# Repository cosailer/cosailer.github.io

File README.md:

cosailer.github.io
==================

welcome to my small site about my projects :-)

you can view this site at http://cosailer.github.io/

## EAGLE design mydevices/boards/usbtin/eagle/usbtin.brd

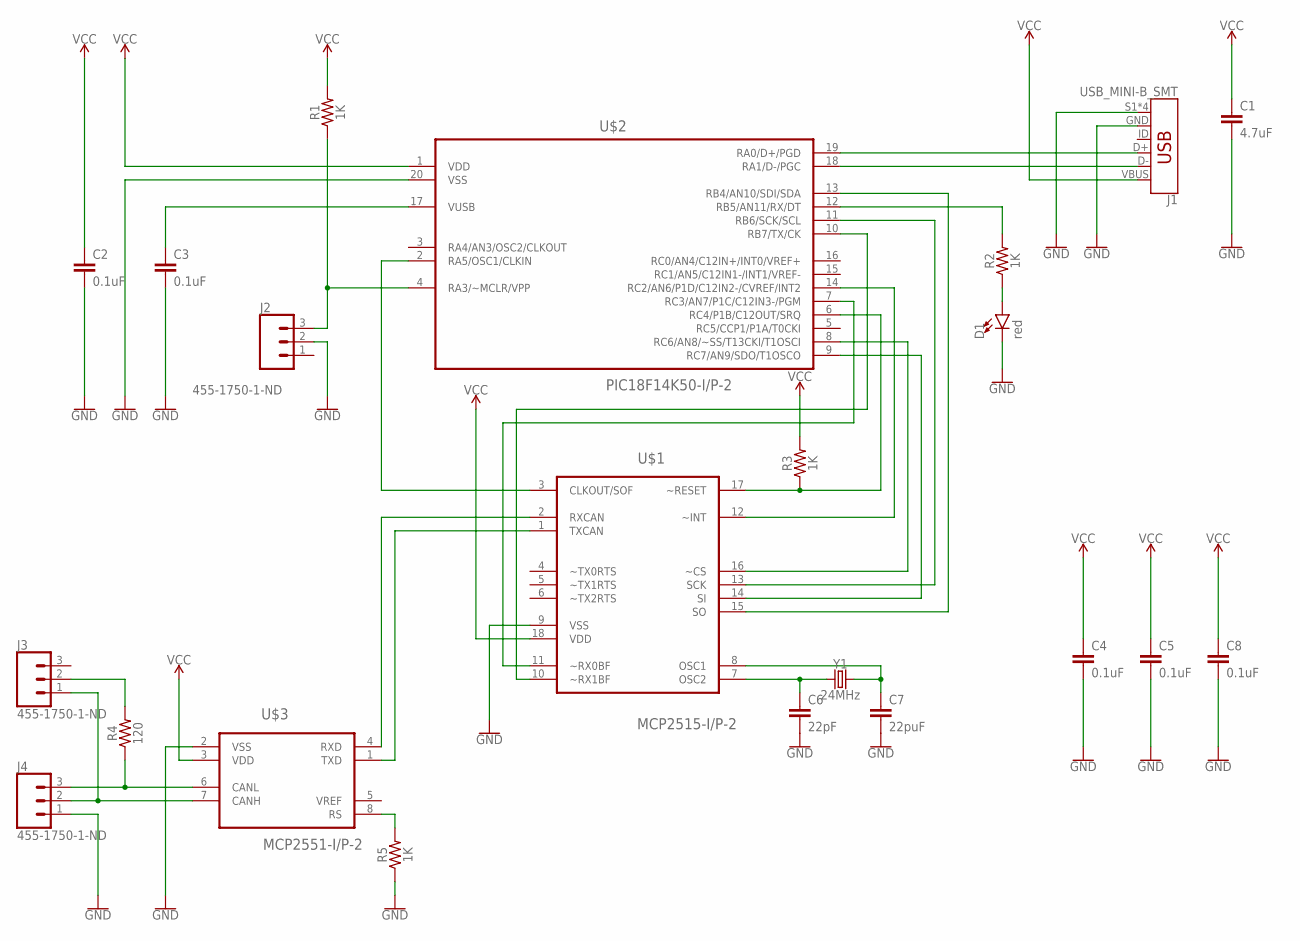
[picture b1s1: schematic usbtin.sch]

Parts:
C1: 4.7uF; 1206
C2, C3, C4, C5, C8: 0.1uF; 0603
C6: 22pF; 0805
C7: 22puF; 0805
D1: red; LED-1206
J1: USB_MINI-B_SMT; USB-MINIB
J2, J3, J4: 455-1750-1-ND; 1X03
R1, R2, R3, R5: 1K; 0805
R4: 120; 0805
U$1: MCP2515-I/P-2; DIP254P762X432-18
U$2: PIC18F14K50-I/P-2; DIP254P762X533-20
U$3: MCP2551-I/P-2; DIP254P762X432-8
Y1: 24MHz; HC49US

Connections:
GND: C1.2, C2.2, C3.2, C4.2, C5.2, C6.2, C7.2, C8.2, D1.C, J1.GND, J1.S1 (SHIELD), J1.S2 (SHIELD), J1.S3 (SHIELD), J1.S4 (SHIELD), J2.2, J4.1, R5.1, U$1.9 (VSS), U$2.20 (VSS), U$3.2 (VSS)
unnamed: J1.D+, U$2.19 (RA0/D+/PGD)
unnamed: J1.D-, U$2.18 (RA1/D-/PGC)
unnamed: C3.1, U$2.17 (VUSB)
unnamed: J2.3, R1.1, U$2.4 (RA3/~MCLR/VPP)
unnamed: U$1.3 (CLKOUT/SOF), U$2.2 (RA5/OSC1/CLKIN)
unnamed: R2.2, U$2.12 (RB5/AN11/RX/DT)
unnamed: R3.1, U$1.17 (~RESET), U$2.6 (RC4/P1B/C12OUT/SRQ)
unnamed: U$1.12 (~INT), U$2.14 (RC2/AN6/P1D/C12IN2-/CVREF/INT2)
unnamed: U$1.16 (~CS), U$2.8 (RC6/AN8/~SS/T13CKI/T1OSCI)
unnamed: D1.A, R2.1
unnamed: U$1.15 (SO), U$2.13 (RB4/AN10/SDI/SDA)
unnamed: U$1.13 (SCK), U$2.11 (RB6/SCK/SCL)
unnamed: U$1.2 (RXCAN), U$3.4 (RXD)
unnamed: U$1.1 (TXCAN), U$3.1 (TXD)
unnamed: R5.2, U$3.8 (RS)
unnamed: C7.1, U$1.8 (OSC1), Y1.2
unnamed: C6.1, U$1.7 (OSC2), Y1.1
unnamed: U$1.11 (~RX0BF), U$2.7 (RC3/AN7/P1C/C12IN3-/PGM)
unnamed: U$1.10 (~RX1BF), U$2.10 (RB7/TX/CK)
unnamed: J3.2, R4.2
unnamed: J3.1, J4.2, U$3.7 (CANH)
unnamed: J4.3, R4.1, U$3.6 (CANL)
unnamed: U$1.14 (SI), U$2.9 (RC7/AN9/SDO/T1OSCO)
VCC: C1.1, C2.1, C4.1, C5.1, C8.1, J1.VBUS, R1.2, R3.2, U$1.18 (VDD), U$2.1 (VDD), U$3.3 (VDD)

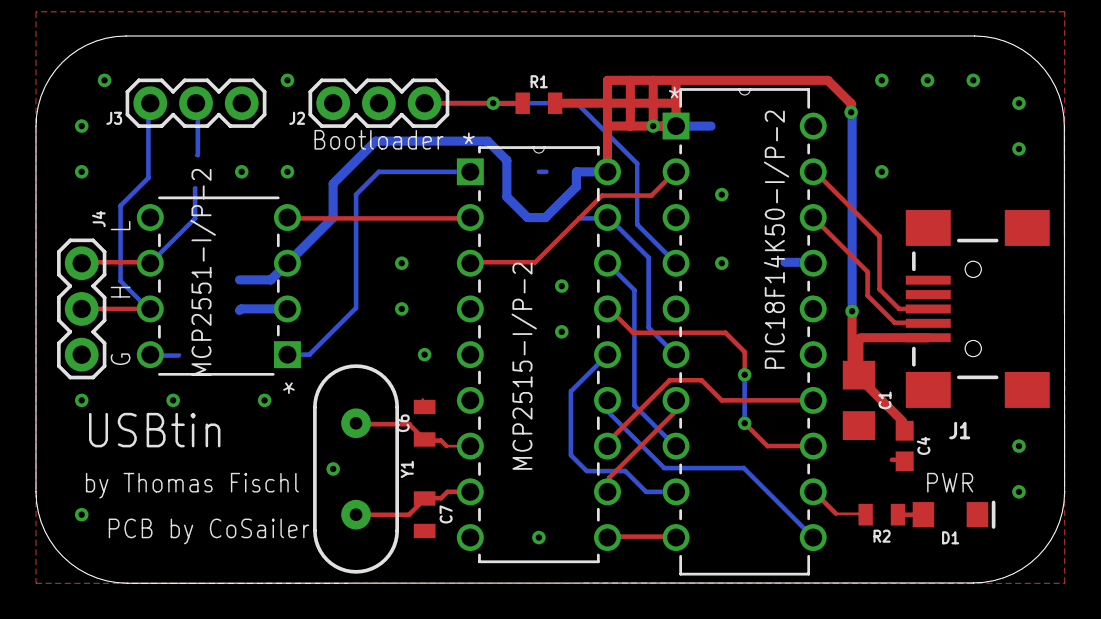
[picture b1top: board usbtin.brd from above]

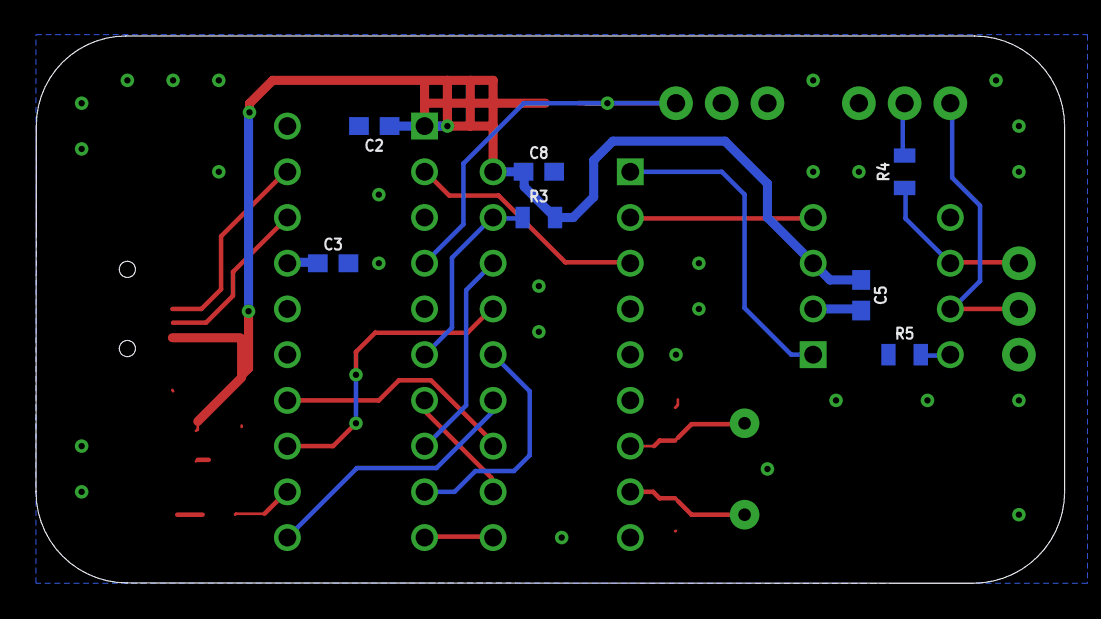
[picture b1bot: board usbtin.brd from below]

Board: 2 copper layers, 57.1 x 30.4 mm, 22 parts (7 on the bottom side), 25 nets.

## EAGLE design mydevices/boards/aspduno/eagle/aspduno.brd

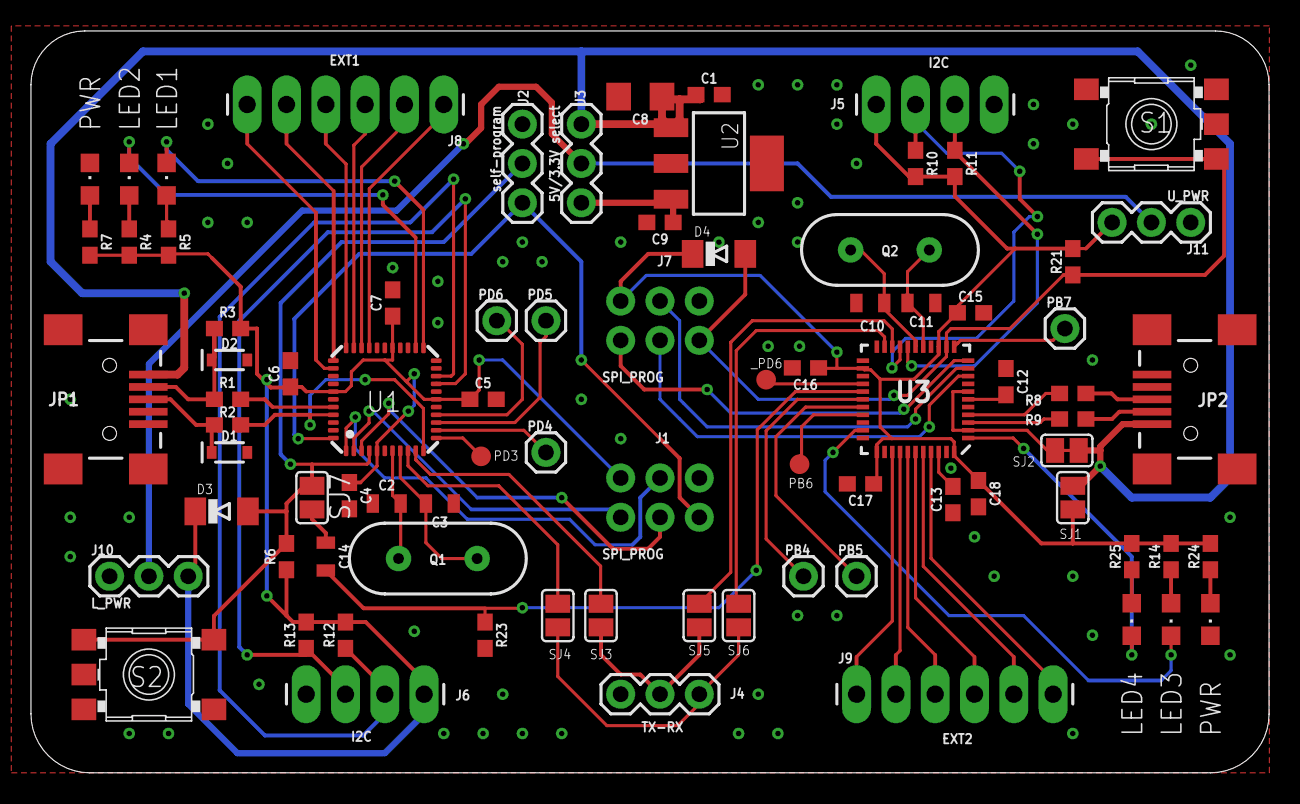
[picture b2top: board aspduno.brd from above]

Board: 2 copper layers, 80.0 x 47.9 mm, 82 parts (0 on the bottom side), 72 nets.

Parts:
C1, C4, C5, C6, C7, C9, C13, C15, C16, C17, C18: 0.1uF; 0603
C2, C3, C10, C11: 22p; 0805
C8: 4.7uF; 1206
C12: 1uF; 0603
C14: 0.1uF; 0805
D1, D2: 3.3V; SOD-323
D3, D4: CD1206-S01575; MINIMELF
J1, J7: SPI_PROG; 2X3-NS
J2: self-program; 1X03
J3: 5V/3.3V select; 1X03
J4: TX-RX; 1X03
J5, J6: I2C; 1X04_LONGPADS
J8: EXT1; 1X06_LONGPADS
J9: EXT2; 1X06_LONGPADS
J10: L_PWR; 1X03
J11: U_PWR; 1X03
JP1, JP2: USB_MINI-B_SMT; USB-MINIB
LED1, LED3, LED4: green; CHIPLED_0805
LED2: red; CHIPLED_0805
LED5: PWR; CHIPLED_0805
PB4, PB5, PB7: 1X01
PB6: TPB1,27; B1,27
PD3: TPB1,27; B1,27
PD4, PD5, PD6: 1X01
PWR: PWR; CHIPLED_0805
Q1: 12Mhz; HC49US
Q2: 16Mhz; HC49US
R1, R2, R8, R9: 68; 0603
R3: 2.2k; 0603
R4, R5, R7, R14, R24, R25: 2K; 0603
R6, R21: 10K; 0603
R10, R11, R12, R13: 4K7; 0603
R23: 1K; 0603
S1, S2: SKHMPSE010; SKHMPXE010
SJ1, SJ2, SJ3, SJ4, SJ5, SJ6, SJ7: SJ
U1: M32L; MLF44
U2: TC1262_VDB; SOT-223-3
U3: 32U4; QFN-44-NOPAD
_PD6: TPB1,27; B1,27

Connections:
3.3V: C9.1, J3.3, U2.3
5V: C1.1, C8.1, J3.1, JP1.VBUS, JP2.VBUS, SJ1.2, SJ2.1, SJ2.2, U2.1, U3.2, U3.7
DTR: C14.2, R23.1, U3.27
GND: C1.2, C2.1, C3.1, C4.2, C5.2, C6.2, C7.2, C8.2, C9.2, C10.1, C11.1, C12.1, C13.1, C15.2, C16.2, C17.2, C18.2, D1.A, D2.A, J1.6, J4.1, J5.4, J6.4, J7.6, JP1.GND, JP1.S1, JP1.S2, JP1.S3, JP1.S4, JP2.GND, JP2.S1, JP2.S2, JP2.S3, JP2.S4, LED5.C, PWR.C, R23.2, S1.1, S1.2, S1.5, S2.1, S2.2, S2.5, U1.6, U1.18, U1.28, U1.39, U2.2, U2.4, U3.5, U3.15, U3.23, U3.33, U3.35, U3.43
MISO: J1.1, U1.2
MOSI: J1.4, U1.1
unnamed: LED1.C, U1.23
unnamed: C14.1, SJ7.2
unnamed: J8.1, U1.30
unnamed: J8.2, U1.31
unnamed: D2.C, JP1.D-, R1.2, R3.1
unnamed: J8.3, U1.32
unnamed: R2.1, U1.11, U1.41
unnamed: D1.C, JP1.D+, R2.2
unnamed: D3.A, J2.2, R6.2, S2.3, S2.4, SJ7.1, U1.4
unnamed: JP2.D+, R8.1
unnamed: PWR.A, R7.1
unnamed: R8.2, U3.4
unnamed: LED2.A, R4.1
unnamed: LED2.C, U1.24
unnamed: R9.2, U3.3
unnamed: R1.1, U1.40
unnamed: JP2.D-, R9.1
unnamed: C10.2, Q2.2, U3.17
unnamed: C11.2, Q2.1, U3.16
unnamed: C13.2, U3.42
unnamed: C12.2, U3.6
unnamed: C2.2, Q1.2, U1.7
unnamed: C3.2, Q1.1, U1.8
unnamed: J5.3, R11.1, U3.18
unnamed: LED1.A, R5.1
unnamed: J6.3, R13.1, U1.19
unnamed: J5.2, R10.1, U3.19
unnamed: J7.1, U3.11
unnamed: J7.4, U3.10
unnamed: LED3.A, R14.1
unnamed: LED3.C, U3.32
unnamed: J7.3, U3.9
unnamed: PB7.1, U3.12
unnamed: PD4.1, U1.13
unnamed: PB6.TP, U3.30
unnamed: J6.2, R12.1, U1.20
unnamed: SJ4.1, U1.9
unnamed: SJ6.1, U3.21
unnamed: D4.A, J7.5, R21.1, S1.3, S1.4, U3.13
unnamed: J8.4, U1.33
unnamed: J8.5, U1.34
unnamed: J8.6, U1.35
unnamed: J9.1, U3.36
unnamed: J9.2, U3.37
unnamed: J9.3, U3.38
unnamed: J9.4, U3.39
unnamed: J9.5, U3.40
unnamed: J9.6, U3.41
unnamed: SJ5.1, U3.20
unnamed: SJ3.1, U1.10
unnamed: PD6.1, U1.15
unnamed: PD5.1, U1.14
unnamed: PD3.TP, U1.12
unnamed: U3.26, _PD6.TP
unnamed: LED4.C, U3.1
unnamed: PB4.1, U3.28
unnamed: PB5.1, U3.29
unnamed: LED5.A, R24.1
unnamed: LED4.A, R25.1
RST: J1.5, J2.3, U1.44
RT0: J4.2, SJ3.2, SJ5.2
RT1: J4.3, SJ4.2, SJ6.2
SCK: J1.3, U1.3
VCC: J3.2, J10.2, J11.2
VDD: C4.1, C5.1, C6.1, C7.1, D3.C, J1.2, J6.1, J10.3, R3.2, R4.2, R5.2, R6.1, R7.2, R12.2, R13.2, U1.5, U1.17, U1.27, U1.38
VEE: C15.1, C16.1, C17.1, C18.1, D4.C, J5.1, J7.2, J11.3, R10.2, R11.2, R14.2, R21.2, R24.2, R25.2, SJ1.1, U3.14, U3.24, U3.34, U3.44

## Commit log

2014-09-15 hello
    world
2014-09-15 main site online
    by CoSailer 2014/09/15
2014-09-15 small changes
    from google drive to github
2014-09-15 small changes
2014-09-16 add nb30 soft mod part
2014-09-16 add df3120
2014-10-09 add new domain
2014-10-09 redo
2014-10-09 new domain
2014-12-01 theme minor tweek
2016-06-17 pages for weichat
2016-09-11 add game section
2016-09-11 add nightfall
2016-09-11 correct some spelling for nightfall
2016-09-12 add video link
2016-09-15 add x220 splash image
2017-09-30 add project
2017-09-30 change readme
2019-03-04 nb30 acc upgrade
2020-05-08 remove music
2020-05-08 add aspduno
2020-05-09 add thesis
2020-05-09 small change
2020-05-09 Create LICENSE
2020-05-09 add bus_pirate
2020-05-09 jpg correction
2020-05-09 add bus blaster
2020-06-13 add 120S, pic, fix dead links
2020-06-24 add msd_boot page

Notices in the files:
parts and their libraries:
SparkFun-Capacitors: Licensing: Creative Commons ShareAlike 4.0 International - https://creativecommons.org/licenses/by-sa/4.0
